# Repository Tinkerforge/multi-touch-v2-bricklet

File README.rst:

Multi Touch Bricklet 2.0
========================

This repository contains the firmware source code and the hardware design
files. The documentation generator configs can be found at
https://github.com/Tinkerforge/generators

Repository Content
------------------

software/:
 * examples/: Examples for all supported languages
 * build/: Compiled files
 * src/: Source code of firmware
 * Makefile: Makefile to build project

hardware/:
 * Contains KiCad project files and additionally schematics as PDF

datasheets/:
 * Contains datasheets for sensors and complex ICs that are used

Hardware
--------

The hardware is designed with the open source EDA Suite KiCad
(http://www.kicad.org). Before you are able to open the files,
you have to install the Tinkerforge kicad-libraries
(https://github.com/Tinkerforge/kicad-libraries). You can either clone
them directly in hardware/ or clone them in a separate folder and
symlink them into hardware/
(ln -s kicad_path/kicad-libraries project_path/hardware). After that you
can open the .pro file in hardware/ with KiCad and from there view and
modify the schematics and the PCB layout.

Software
--------

If you want to do your own Brick/Bricklet firmware development we highly
recommend that you use our build environment setup script and read the
tutorial (https://www.tinkerforge.com/en/doc/Tutorials/Tutorial_Build_Environment/Tutorial.html).

To compile the C code we recommend you to install the newest GNU Arm Embedded
Toolchain (https://launchpad.net/gcc-arm-embedded/+download).
You also need to install bricklib2 (https://github.com/Tinkerforge/bricklib2).

You can either clone it directly in software/src/ or clone it in a
separate folder and symlink it into software/src/
(ln -s bricklib_path/bricklib2 project_path/software/src/). Finally make sure to
have CMake installed (http://www.cmake.org/cmake/resources/software.html).

After that you can build the firmware by invoking make in software/.
The firmware (.zbin) can then be found in software/build/ and uploaded
with brickv (click button "Flashing" on start screen).

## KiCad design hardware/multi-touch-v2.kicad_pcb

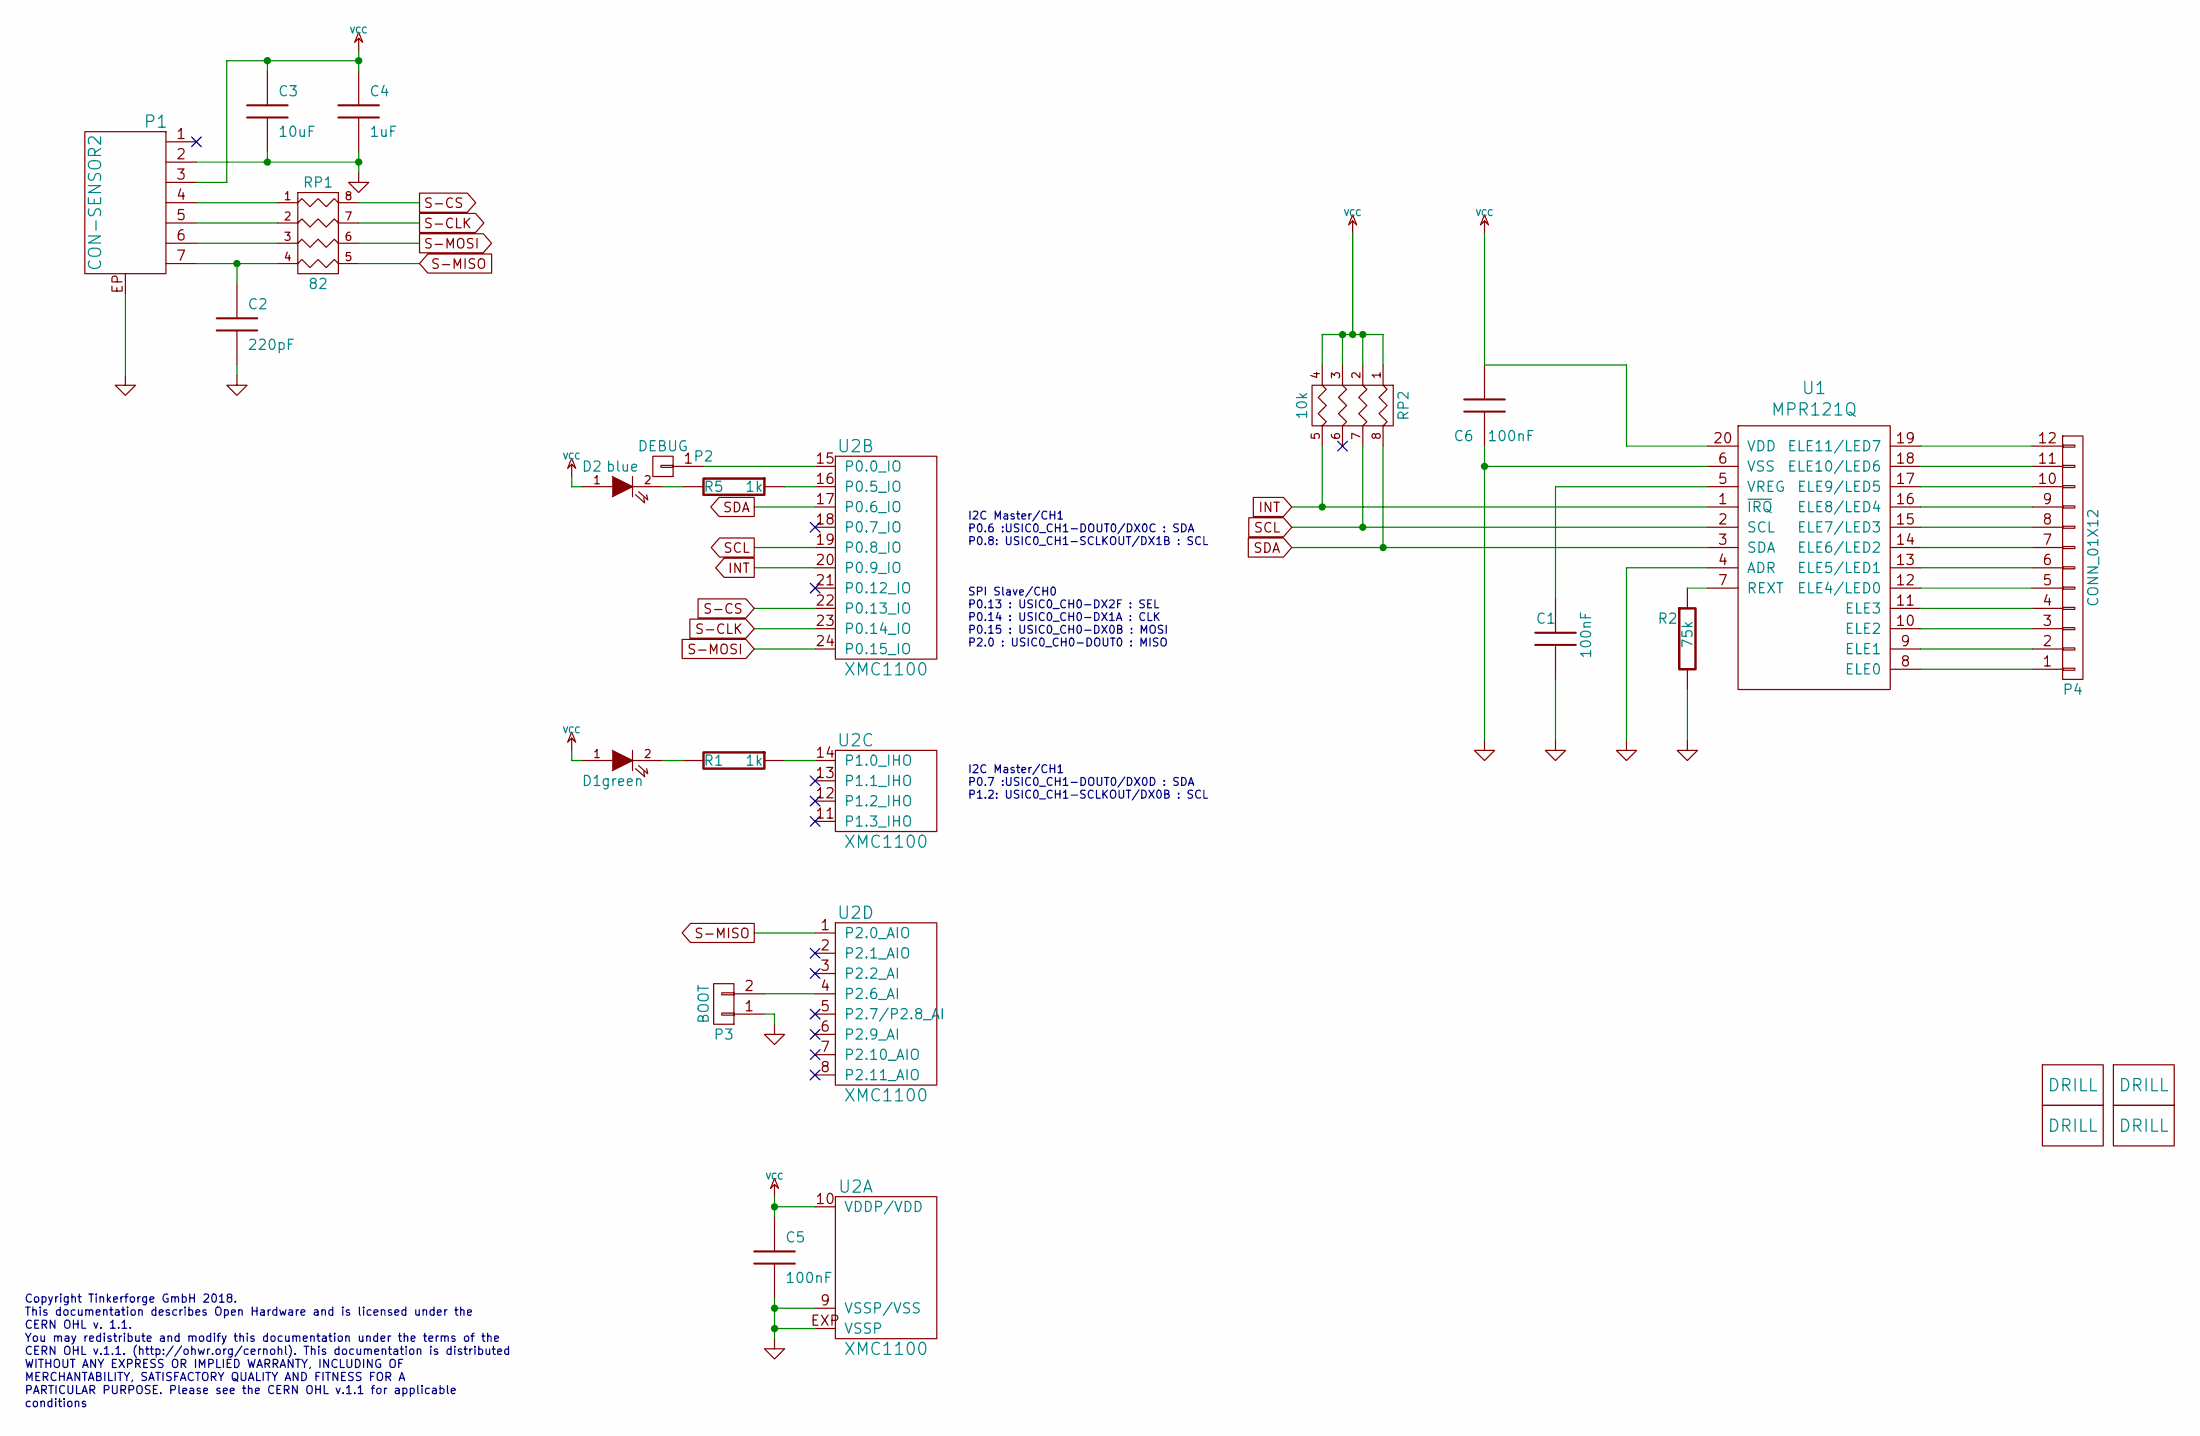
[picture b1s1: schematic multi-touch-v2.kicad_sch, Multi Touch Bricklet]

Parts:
C1, C5, C6: 100nF; C0603F
C2: 220pF; C0402F
C3: 10uF; C0805
C4: 1uF; C0603F
D1: green; D0603F
D2: blue; D0603F
P1: CON-SENSOR2
P2: DEBUG; DEBUG_PAD
P3: BOOT; SolderJumper
P4: CONN_01X12; pin_array_6x2
R1, R5: 1k; R0603F
R2: 75k; R0603F
RP1: 82; 4X0402
RP2: 10k; 4X0402
U1: MPR121Q; QFN20-3X3
U2: XMC1100; QFN24-4x4mm-0.5mm
U3, U4, U5, U6: DRILL; DRILL_NP

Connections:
GND: C1.2, C2.2, C3.2, C4.2, C5.2, C6.1, P1.2, P1.EP, P3.1, R2.2, U1.4 (ADR), U1.6 (VSS), U2.9 (VSSP/VSS), U2.EXP (VSSP)
INT: RP2.5 (R4), U1.1 (~IRQ), U2.20 (P0.9_IO)
unnamed: C1.1, U1.5 (VREG)
unnamed: C2.1, P1.7, RP1.4
unnamed: D1.2 (K), R1.2
unnamed: D2.2 (K), R5.2
unnamed: P1.4, RP1.1
unnamed: P1.5, RP1.2
unnamed: P1.6, RP1.3
unnamed: P2.1, U2.15 (P0.0_IO)
unnamed: P3.2, U2.4 (P2.6_AI)
unnamed: P4.1, U1.8 (ELE0)
unnamed: P4.2, U1.9 (ELE1)
unnamed: P4.3, U1.10 (ELE2)
unnamed: P4.4, U1.11 (ELE3)
unnamed: P4.5, U1.12 (ELE4/LED0)
unnamed: P4.6, U1.13 (ELE5/LED1)
unnamed: P4.7, U1.14 (ELE6/LED2)
unnamed: P4.8, U1.15 (ELE7/LED3)
unnamed: P4.9, U1.16 (ELE8/LED4)
unnamed: P4.10, U1.17 (ELE9/LED5)
unnamed: P4.11, U1.18 (ELE10/LED6)
unnamed: P4.12, U1.19 (ELE11/LED7)
unnamed: R1.1, U2.14 (P1.0_IHO)
unnamed: R2.1, U1.7 (REXT)
unnamed: R5.1, U2.16 (P0.5_IO)
S-CLK: RP1.7 (R2), U2.23 (P0.14_IO)
S-CS: RP1.8 (R1), U2.22 (P0.13_IO)
S-MISO: RP1.5 (R4), U2.1 (P2.0_AIO)
S-MOSI: RP1.6 (R3), U2.24 (P0.15_IO)
SCL: RP2.7 (R2), U1.2 (SCL), U2.19 (P0.8_IO)
SDA: RP2.8 (R1), U1.3 (SDA), U2.17 (P0.6_IO)
VCC: C3.1, C4.1, C5.1, C6.2, D1.1 (A), D2.1 (A), P1.3, RP2.1, RP2.2, RP2.3, RP2.4, U1.20 (VDD), U2.10 (VDDP/VDD)

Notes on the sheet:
SPI Slave/CH0 P0.13 : USIC0_CH0-DX2F : SEL P0.14 : USIC0_CH0-DX1A : CLK P0.15 : USIC0_CH0-DX0B : MOSI P2.0 : USIC0_CH0-DOUT0 : MISO
I2C Master/CH1 P0.6 :USIC0_CH1-DOUT0/DX0C : SDA P0.8: USIC0_CH1-SCLKOUT/DX1B : SCL
I2C Master/CH1 P0.7 :USIC0_CH1-DOUT0/DX0D : SDA P1.2: USIC0_CH1-SCLKOUT/DX0B : SCL
Copyright Tinkerforge GmbH 2018. This documentation describes Open Hardware and is licensed under the CERN OHL v. 1.1. You may redistribute and modify this documentation under the terms of the CERN OHL v.1.1. (http://ohwr.org/cernohl). This documentation is distributed WITHOUT ANY EXPRESS OR IMPLIE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

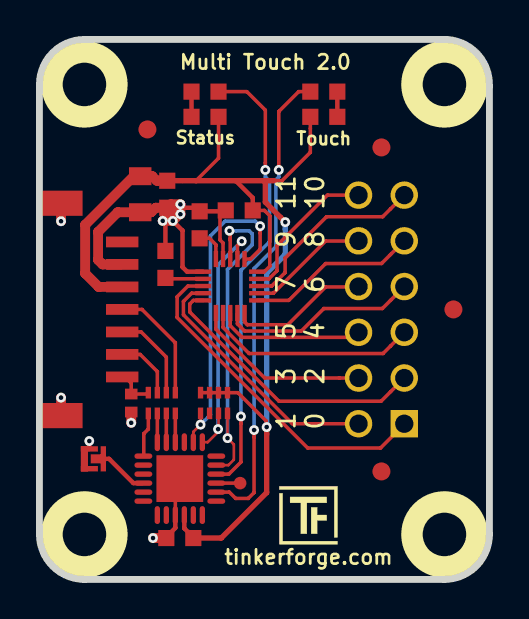
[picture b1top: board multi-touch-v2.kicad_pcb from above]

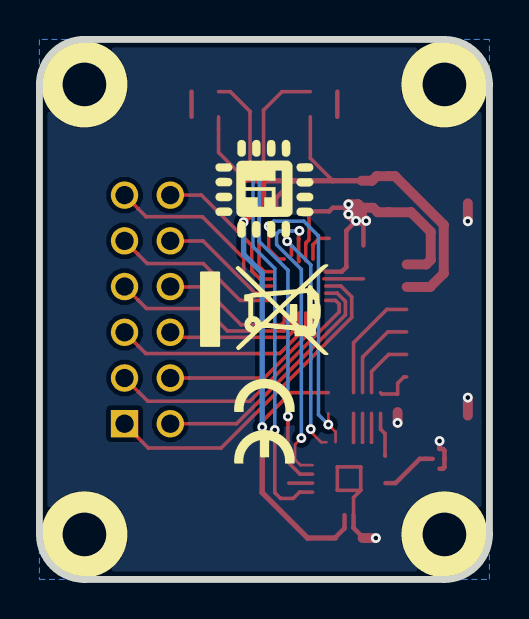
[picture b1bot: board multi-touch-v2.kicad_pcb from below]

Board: 2 copper layers, 25.0 x 30.0 mm, 29 parts (2 on the bottom side), 33 nets.

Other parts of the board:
Fiducial_Mark: VAL**; Fiducial_Mark
Fiducial_Mark#2, Fiducial_Mark#3, Fiducial_Mark#4: VAL**; Fiducial_Mark
VAL: WEEE_7mm
VAL#2: CE_5mm

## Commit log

2018-06-27 Add datasheet
2018-06-27 Add current status (broken)
2018-07-04 Fix schematic
2018-07-04 Add layout
2018-07-04 Fix page settings
2018-07-06 Add 3d information
2018-07-06 Fix logos
2018-07-06 Fix readme
2018-07-06 Add .gitignore
2018-07-11 Fix origin
2018-07-27 Add auto-generated stub firmware
2019-03-11 fixed library and schematic
2019-03-11 changed touch controller to MPR121Q
2019-03-11 changed footprint of MPR121Q from QFN-20-3x3 to QFN20-3x3
2019-04-04 changed "touch" led from blue to green
2019-04-09 Exchange CPT112S by MPR121 datasheet
2019-04-09 Add API implementation and driver for MPR121
    This is mostly adapted from Multi Touch Bricklet V1
2019-04-09 Allow touch state of touch LED to be handled outside of led_flicker function
2019-05-03 Add auto-generated examples
2019-05-14 Update rust examples.
2019-08-14 Turn logging off
2019-08-14 Add changelog entry for inital version
2019-08-15 add 3d data
2019-08-15 add schematic
2019-08-22 c: Adapt to bindings changes
2019-08-22 Remove development marker
2019-08-23 Use correct state type for examples.
2020-01-13 examples: Use python3 input instead of python2 raw_input.
2020-01-13 examples: mqtt: Remove trailing whitespace.
2020-08-19 Add uc examples.
2020-08-25 uc: Fix whitespace
2020-08-27 uc: Fix warnings.
2020-09-02 uc: Add example driver note.
2021-05-06 mathematica: Fix broken syntax
2021-10-25 Update KiCad link
    https://www.kicad.org/blog/2021/10/Avoid-links-to-former-kicad-domain/
2022-04-19 examples: uc: Rename TF_HalContext to TF_HAL.
2022-04-27 uc: Adapt to bindings changes
2022-05-10 go: Fix format string
2022-07-06 Add license files.
2023-06-20 update to new kicad version
2025-10-04 Fix compatibility with new Docker build image (GCC 14.2.1)

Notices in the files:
hardware/multi-touch-v2.kicad_pcb:
Licensed under CERN OHL v.1.1
Copyright (©) 2018, L.Lauer
